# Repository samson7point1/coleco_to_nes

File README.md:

# ColecoVision to NES Controller PCB Replacement
This PCB is designed to be swapped out with that of a standard NES controller to allow you to use it with a ColecoVision game console.  As this is a drop-in replacement, there is no need to modify or damage any of the original components of the NES controller.

## Bill of Materials
* 1 x DE9 Joystick cable (https://console5.com/store/atari-sega-commodore-coleco-msx-6-1-8m-joystick-controller-project-repair-cable-cord.html)
* 11 x 1N4148 Switching Diodes (https://www.mouser.com/ProductDetail/512-1N4148)
* 1 x 4 Position, Low-Profile DIP switch (https://www.mouser.com/ProductDetail/653-A6S-4104-H)
* 1 x OEM NES Control Pad (First Party NES Classic Control Pads may also work)

The board populated (Note the DIP positions have set the Select button to "5"):

The board wired and installed:

## Notes / Features
* I reversed the left and right fire buttons from the ColecoVision controller so that the NES "B" button corresponds with the right fire button, and the NES "A" button corresponds with the left.  I initially did this because it made Donkey Kong play closer to the NES version, but I found overall it also worked better for nearly every game I tried.
* The NES "Start" button is mapped to the number pad's "1" button because almost every game requires pressing "1" to start.
* The NES "Select" button can be mapped with the DIP switch on the back

[Test Video - click link then select "View Raw"](TESTING.MOV)
## Mapping the "Select Button"

A handful of games require you to press some button other than "1" to start - for example Mario Bros. requires that you use "5" to add credits before you can play.  Because of this I thought it would be useful if you could just pick which button you want "Select" to imitate.  The settings are actually printed on the PCB, but I thought I'd include them here for reference.

| CV Button | 1 | 2 | 3 | 4 |
|-----------|---|---|---|---|
|         * |   | ↑ |   | ↑ |
|         0 | ↑ | ↑ |   |   |
|         1 |   |   |   | ↑ |
|         2 |   |   | ↑ |   |
|         3 | ↑ |   |   | ↑ |
|         4 | ↑ | ↑ | ↑ |   |
|         5 |   | ↑ | ↑ |   |
|         6 | ↑ |   |   |   |
|         7 |   |   | ↑ | ↑ |
|         8 |   | ↑ | ↑ | ↑ |
|         9 |   | ↑ |   |   |
|         # | ↑ |   | ↑ |   |

## License
This work is licensed under a [Creative Commons Attribution-NonCommercial-ShareAlike 4.0 International License](http://creativecommons.org/licenses/by-nc-sa/4.0/).

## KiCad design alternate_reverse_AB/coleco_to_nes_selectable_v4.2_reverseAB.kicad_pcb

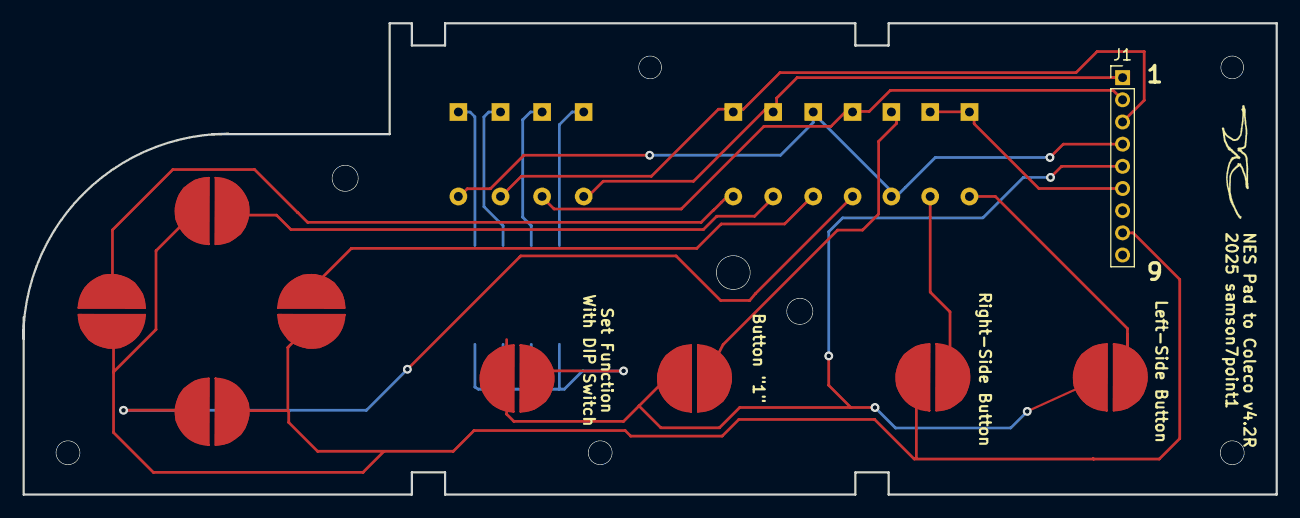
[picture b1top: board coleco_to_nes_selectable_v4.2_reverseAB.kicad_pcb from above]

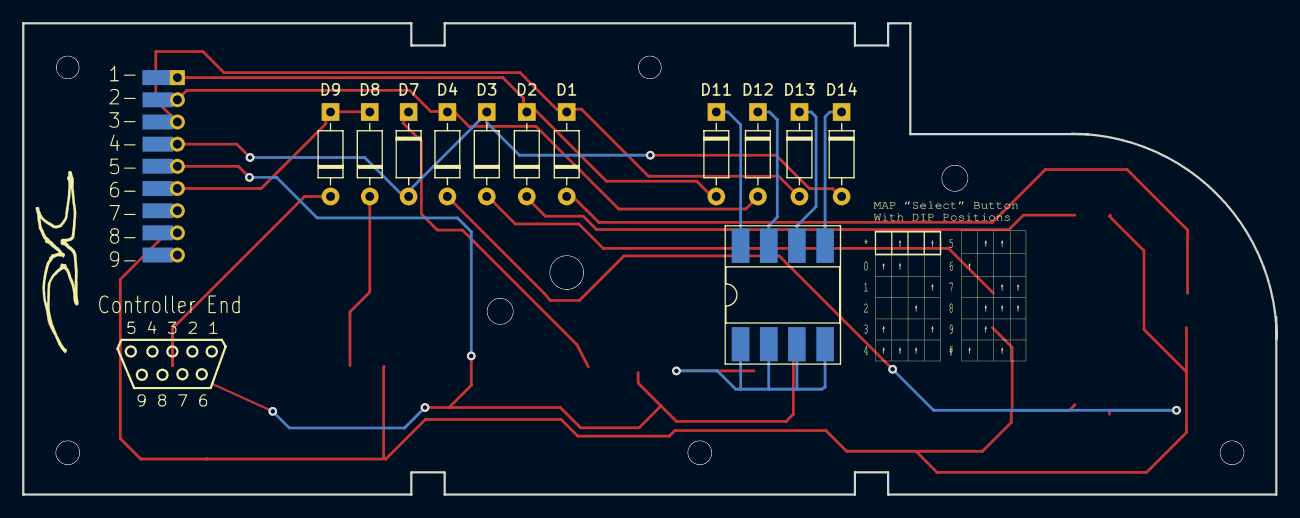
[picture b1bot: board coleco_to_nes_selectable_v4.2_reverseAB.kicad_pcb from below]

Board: 2 copper layers, 113.0 x 42.5 mm, 21 parts (12 on the bottom side), 19 nets.

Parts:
Button-1: SW_Push; Contact_Pad_Vertical_Split
Button-*1: SW_Push; Contact_Pad_Vertical_Split
Button-Side-L1: SW_Push; Contact_Pad_Vertical_Split
Button-Side-R1: SW_Push; Contact_Pad_Vertical_Split
D1, D2, D3, D4, D8, D9: DIODE; D_DO-35_SOD27_P7.62mm_Horizontal_reverse_polarity
D7, D11, D12, D13, D14: DIODE; D_DO-35_SOD27_P7.62mm_Horizontal
D-Down1: SW_Push; Contact_Pad_Vertical_Split
D-Left1: SW_Push; Contact_Pad_Vertical_Split
D-Right1: SW_Push; Contact_Pad_Vertical_Split
D-Up1: D-Up; Contact_Pad_Vertical_Split
J1: Conn_01x09_Male; PinHeader_1x09_P2.00mm_Vertical_With_Pads
SW1: SW_DIP_x04; DIP-8_W8.89mm_SMDSocket_LongPads

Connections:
unnamed: Button-1.1, D7.1
unnamed: Button-*1.1, SW1.1, SW1.2, SW1.3, SW1.4
unnamed: Button-1.2, Button-*1.2, Button-Side-L1.1, J1.5
unnamed: D-Down1.1, D-Left1.1, D-Right1.1, D-Up1.1, J1.8
unnamed: Button-Side-L1.2, Button-Side-R1.1, D9.2
unnamed: Button-Side-R1.2, D8.2
unnamed: D1.1, D13.2, J1.3
unnamed: D8.1, D9.1, J1.6
unnamed: D11.1, SW1.8
unnamed: D2.1, D11.2, J1.1
unnamed: D12.1, SW1.7
unnamed: D4.1, D12.2, J1.2
unnamed: D13.1, SW1.6
unnamed: D14.1, SW1.5
unnamed: D3.1, D7.2, D14.2, J1.4
unnamed: D4.2, D-Down1.2
unnamed: D1.2, D-Left1.2
unnamed: D3.2, D-Right1.2
unnamed: D2.2, D-Up1.2

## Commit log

2020-06-05 added images
2020-06-05 trying to fix images
2020-06-05 fixing images
2020-06-05 fixed images
2020-06-05 cleanup
2021-10-05 Fix "edge not closed" warnings on PCB
2025-06-23 Added an alternate version where the left and right buttons on the NES pad match the orientation of the triggers on the Coleco controller - the default design reverses this.
